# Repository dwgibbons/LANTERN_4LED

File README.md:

# LANTERN_4LED

Hardware for a Dietz oil based lantern converted to LED powered.

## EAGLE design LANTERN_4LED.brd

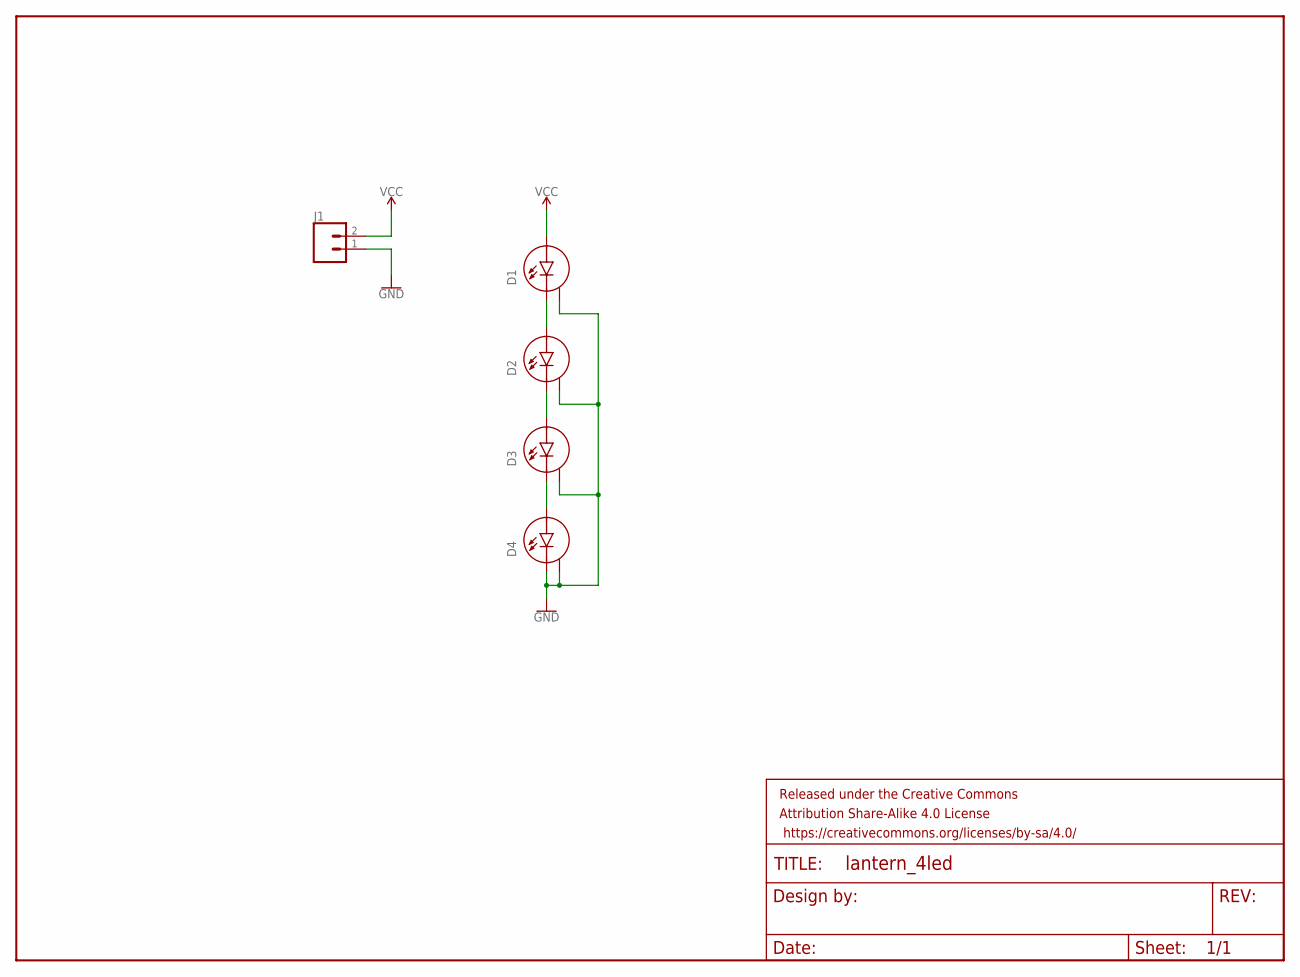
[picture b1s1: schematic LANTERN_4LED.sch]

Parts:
D1, D2, D3, D4: LED_H1414_H; LED_1414
FRAME1: FRAME-LETTERNO_PACKAGE; DUMMY
J1: CONN_02PTH3; 1X02_LONGPADS

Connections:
GND: D1.H, D2.H, D3.H, D4.C, D4.H, J1.1
unnamed: D1.C, D2.A
unnamed: D2.C, D3.A
unnamed: D3.C, D4.A
VCC: D1.A, J1.2

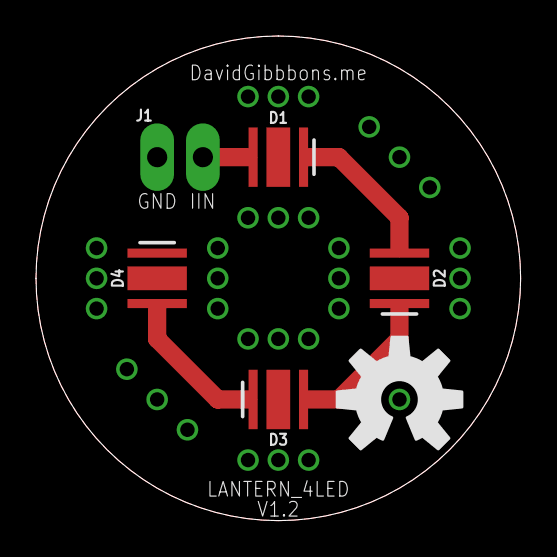
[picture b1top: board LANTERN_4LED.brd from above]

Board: 2 copper layers, 26.9 x 26.9 mm, 7 parts (0 on the bottom side), 5 nets.

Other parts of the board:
U$1: OSHW-LOGO-L

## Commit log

2017-03-14 :circus_tent: Added .gitattributes & .gitignore files
2017-03-14 Initial design to test LED parameters and reactivity
2017-03-17 Designed for 2 layer board
2017-03-17 Tied the heatsinks to ground.

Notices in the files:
parts and their libraries:
SparkFun-Connectors: Licensing: Creative Commons ShareAlike 4.0 International - https://creativecommons.org/licenses/by-sa/4.0
SparkFun-Aesthetics: Released under the Creative Commons Attribution Share-Alike 4.0 License
SparkFun-Aesthetics: https://creativecommons.org/licenses/by-sa/4.0
